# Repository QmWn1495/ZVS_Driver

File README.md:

# ZVS Driver

## What
This is a ZVS(Zero Voltage Switching) Mazzalli circuit

## Why
A Zero Voltage Switching driver is usually made to efficiently drive high frequency power electronics. In this case, it will be used to drive a High Voltage AC Transformer, which will be used to drive a CW(Cockcroft-Walton) Voltage Multiplier.

## Schematic

Full schematic, contains Input(J1, F1, C3, C4), Feed Choke(L1; rated 13.5A at 47uH), Switches(Q1, Q2; both IRFP250N), Gate Driving and Protection(R1, R2, R3, R4, D1, D2, D3, D4), and the Resonant tank(J1, C1, C2; C1||C2)

## PCB

2-layer board, 68mm x 55.8mm, all components on top side. All the traces were routed on F.Cu in order to allow for a solid GND pour on B.Cu. 2oz copper is needed for this board to operate at full rating(10A, meaning ~14A peak). The drain nets keep a minimum 0.8mm clearance to account for the ~94V peak.

## 3D Model

(From KiCad's 3D Viewer)

## Wiring Diagram

Diagram drawn from circuit-diagram.org(great website!!)

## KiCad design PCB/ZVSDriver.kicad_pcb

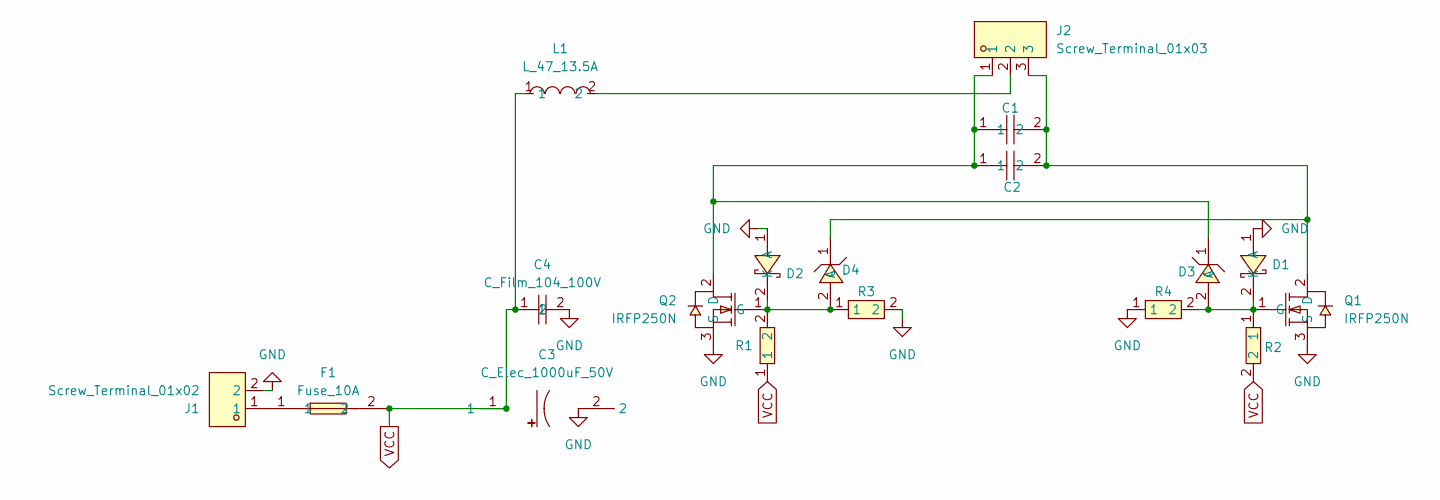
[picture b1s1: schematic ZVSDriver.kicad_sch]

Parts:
C1, C2: C_Film_334_630V; CAP-TH_L18.0-W7.5-P15.00-D1.2; MPN MPP334J2J15AJ22800; LCSC Part C506837
C3: C_Elec_1000uF_50V; CAP-TH_BD12.5-P5.00-D0.6-FD; MPN ECR1HBK102MLL125025; LCSC Part C233103
C4: C_Film_104_100V; CAP-TH_L7.2-W2.5-P5.00-D0.5; MPN B32529C1104J289; LCSC Part C15523
D1, D2: 1N4742A; DO-41_BD2.4-L4.7-P8.70-D0.8-FD; MPN 1N4742A-TAP; LCSC Part C6369271
D3, D4: UF4007-E3/54; DO-41_BD2.4-L4.7-P8.70-D0.9-RD; MPN UF4007-E3/54; LCSC Part C511041
F1: Fuse_10A; FUSE-TH_L19.1-W5.1; MPN 0287010.PXCN; LCSC Part C142683
J1: Screw_Terminal_01x02; CONN-TH_XY126V-5.0-2P; MPN XY126V-5.0-2P; LCSC Part C557646
J2: Screw_Terminal_01x03; CONN-TH_XY126V-5.0-3P; MPN XY126V-5.0-3P; LCSC Part C557647
L1: L_47_13.5A; IND-TH_L23.0-W12.0-P9.00-D1.4; MPN PDMTAT068125-470MLU; LCSC Part C3011541
Q1, Q2: IRFP250N; TO-247AC-3_L15.8-W5.0-P5.46-L; MPN IRFP250NPBF; LCSC Part C2580
R1, R2: MOF3WS-470Ω±5% T; RES-TH_BD5.0-L15.5-P19.50-D0.7; MPN MOF3WS-470Ω±5% T; LCSC Part C121824
R3, R4: RN 1/4W 10K F T/B A1; RES-TH_BD2.5-L6.5-P10.50-D0.6; MPN RN1/4W10KFT/BA1; LCSC Part C410695

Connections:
GND: C3.2, C4.2, D1.1 (A), D2.1 (A), J1.2, Q1.3 (S), Q2.3 (S), R3.2, R4.1
unnamed: D1.2 (K), D3.2 (A), Q1.1 (G), R2.1, R4.2
unnamed: D2.2 (K), D4.2 (A), Q2.1 (G), R1.2, R3.1
unnamed: C1.1, C2.1, D3.1 (C), J2.1, Q2.2 (D)
unnamed: C1.2, C2.2, D4.1 (C), J2.3, Q1.2 (D)
unnamed: F1.1, J1.1
unnamed: J2.2, L1.2
VCC: C3.1, C4.1, F1.2, L1.1, R1.1, R2.2

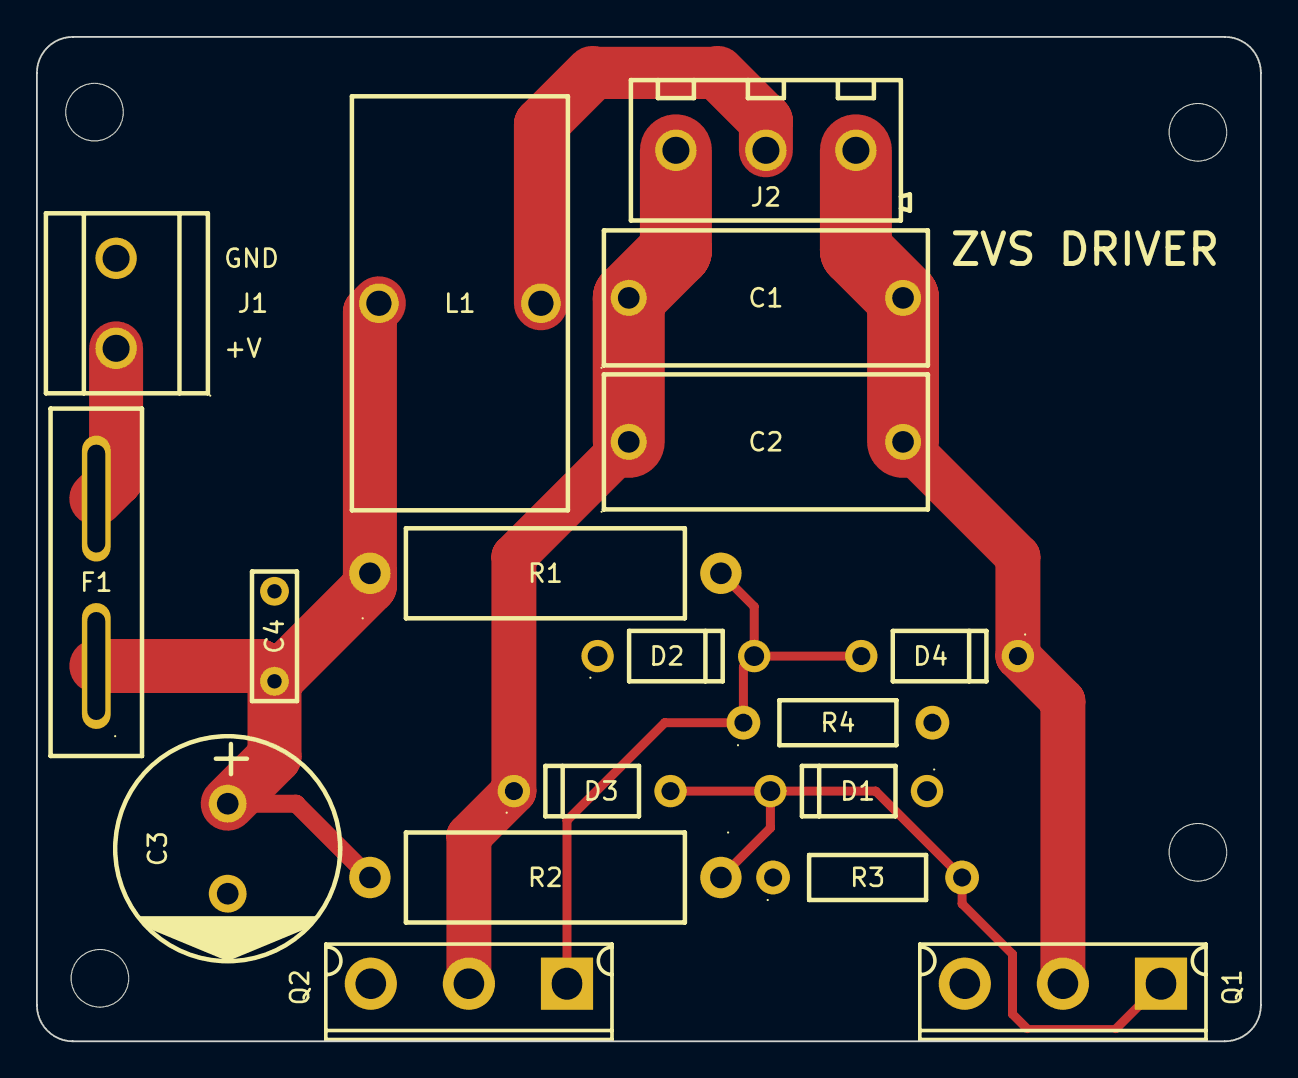
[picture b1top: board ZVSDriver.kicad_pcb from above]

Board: 2 copper layers, 68.0 x 55.8 mm, 22 parts (0 on the bottom side), 8 nets.

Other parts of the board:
H1, H2, H3, H4: MountingHole_M3; MountingHole_3.2mm_M3
